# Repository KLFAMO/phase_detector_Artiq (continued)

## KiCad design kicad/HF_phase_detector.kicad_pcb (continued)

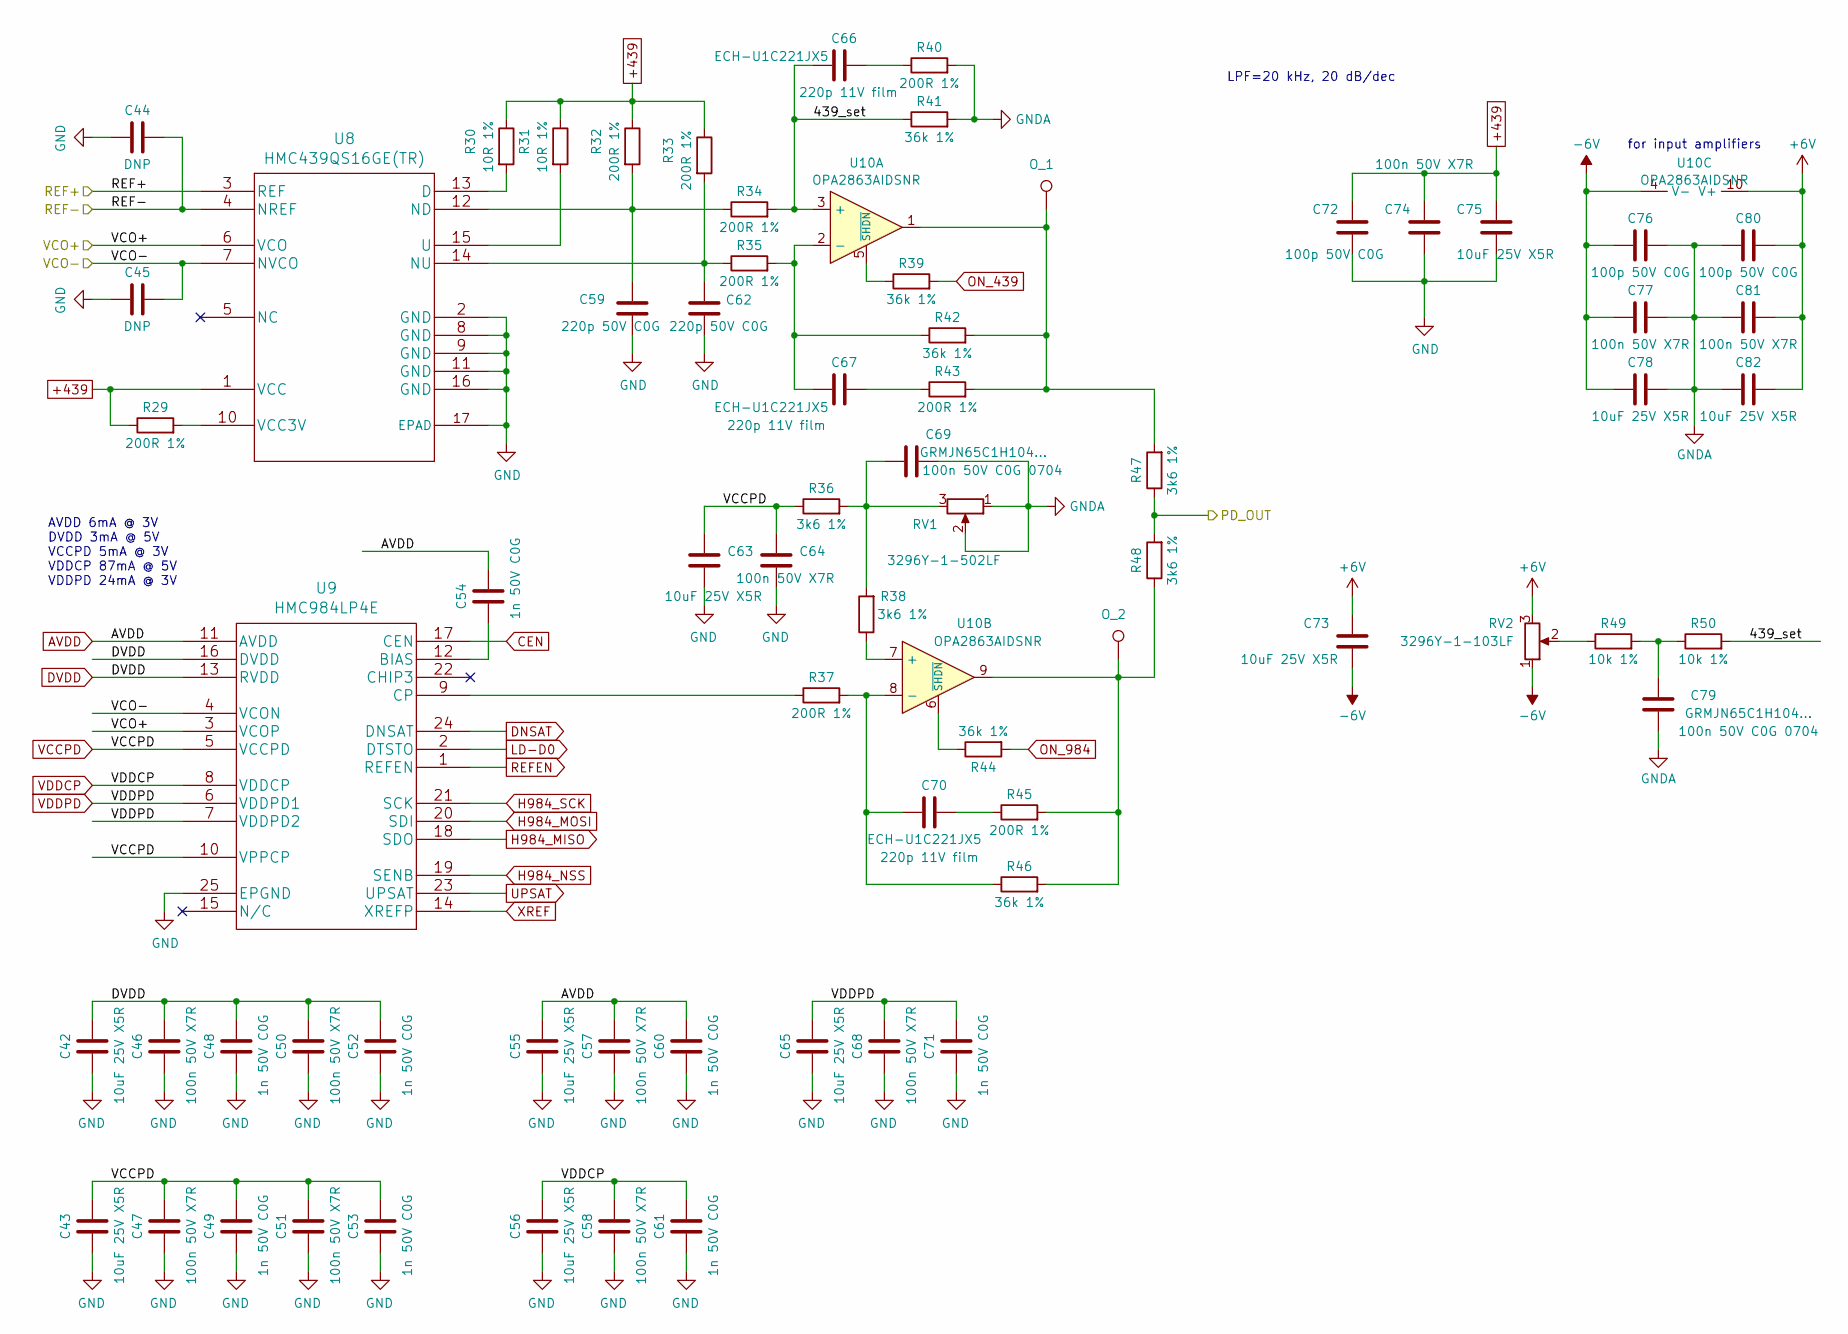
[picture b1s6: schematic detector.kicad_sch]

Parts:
C42, C43, C55, C56, C63, C65, C73, C75, C78, C82: GRM188R61E106KA73; C_0603_1608Metric
C44, C45: DNP; C_0603_1608Metric
C46, C47, C50, C51, C57, C58, C64, C68, C74, C77, C81: 100n 50V X7R; C_0603_1608Metric
C48, C49, C52, C53, C54, C60, C61, C71: 1n 50V C0G; C_0603_1608Metric
C59, C62: 220p 50V C0G; C_0603_1608Metric
C66, C67, C70: ECH-U1C221JX5; C_0603_1608Metric
C69, C79: GRMJN65C1H104...; C_0805_2012Metric
C72, C76, C80: 100p 50V C0G; C_0603_1608Metric
O_1, O_2: TestPoint; TestPoint_THTPad_1.5x1.5mm_Drill0.7mm
R29: 200R 1%; R_0805_2012Metric
R30, R31: 10R 1%; R_0603_1608Metric
R32, R33, R34, R35, R37, R40, R43, R45: 200R 1%; R_0603_1608Metric
R36, R38, R47, R48: 3k6 1%; R_0603_1608Metric
R39, R41, R42, R44, R46: 36k 1%; R_0603_1608Metric
R49, R50: 10k 1%; R_0603_1608Metric
RV1: 3296Y-1-502LF; Potentiometer_Bourns_3296Y_Vertical
RV2: 3296Y-1-103LF; Potentiometer_Bourns_3296Y_Vertical
U8: HMC439QS16GE(TR); QS16GE_ADI
U9: HMC984LP4E; QFN-24-1EP_4x4mm_P0.5mm_EP2.15x2.15mm_ThermalVias
U10: OPA2863AIDSNR; DFN-10-1EP_3x3mm_P0.5mm_EP1.65x2.38mm_ThermalVias

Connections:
/DIV14-: C44.1, U8.4 (NREF); also elsewhere on the board
/DIV24+: U8.6 (VCO), U9.3 (VCOP); also elsewhere on the board
/DIV24-: C45.1, U8.7 (NVCO), U9.4 (VCON); also elsewhere on the board
/PI and outputs/PD_OUT_set: R47.1, R48.2; also elsewhere on the board
/Phase detector/439_set: C66.1, R34.2, R41.1, R50.2, U10.3 (+)
AVDD: C54.2, C55.2, C57.1, C60.1, U9.11 (AVDD); also elsewhere on the board
CEN: U9.17 (CEN); also elsewhere on the board
DNSAT: U9.24 (DNSAT); also elsewhere on the board
DVDD: C42.2, C46.1, C48.1, C50.1, C52.1, U9.13 (RVDD), U9.16 (DVDD); also elsewhere on the board
H984_MISO: U9.18 (SDO); also elsewhere on the board
H984_MOSI: U9.20 (SDI); also elsewhere on the board
H984_NSS: U9.19 (SENB); also elsewhere on the board
H984_SCK: U9.21 (SCK); also elsewhere on the board
LD-D0: U9.2 (DTSTO); also elsewhere on the board
unnamed: C66.2, R40.1
unnamed: C67.2, R43.1
unnamed: C69.1, R36.2, R38.2, RV1.3
unnamed: C70.2, R45.1
unnamed: C79.1, R49.2, R50.1
unnamed: O_1.1, R42.2, R43.2, R47.2, U10.1
unnamed: O_2.1, R45.2, R46.2, R48.1, U10.9
unnamed: R49.1, RV2.2
unnamed: R30.2, U8.13 (D)
unnamed: C59.2, R32.2, R34.1, U8.12 (ND)
unnamed: C62.2, R33.2, R35.1, U8.14 (NU)
unnamed: R31.2, U8.15 (U)
unnamed: R29.2, U8.10 (VCC3V)
unnamed: C54.1, U9.12 (BIAS)
unnamed: R37.1, U9.9 (CP)
unnamed: C67.1, R35.2, R42.1, U10.2 (-)
unnamed: R39.1, U10.5 (~SHDN)
unnamed: R38.1, U10.7 (+)
unnamed: C70.1, R37.2, R46.1, U10.8 (-)
unnamed: R44.1, U10.6 (~SHDN)
ON_439: R39.2; also elsewhere on the board
ON_984: R44.2; also elsewhere on the board
REFEN: U9.1 (REFEN); also elsewhere on the board
UPSAT: U9.23 (UPSAT); also elsewhere on the board
VCCPD: C43.2, C47.1, C49.1, C51.1, C53.1, C63.2, C64.1, R36.1, U9.5 (VCCPD), U9.10 (VPPCP); also elsewhere on the board
VDDCP: C56.2, C58.1, C61.1, U9.8 (VDDCP); also elsewhere on the board
VDDPD: C65.2, C68.1, C71.1, U9.6 (VDDPD1), U9.7 (VDDPD2); also elsewhere on the board
XREF: U9.14 (XREFP); also elsewhere on the board

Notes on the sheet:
AVDD 6mA @ 3V DVDD 3mA @ 5V VCCPD 5mA @ 3V VDDCP 87mA @ 5V VDDPD 24mA @ 3V
for input amplifiers
LPF=20 kHz, 20 dB/dec

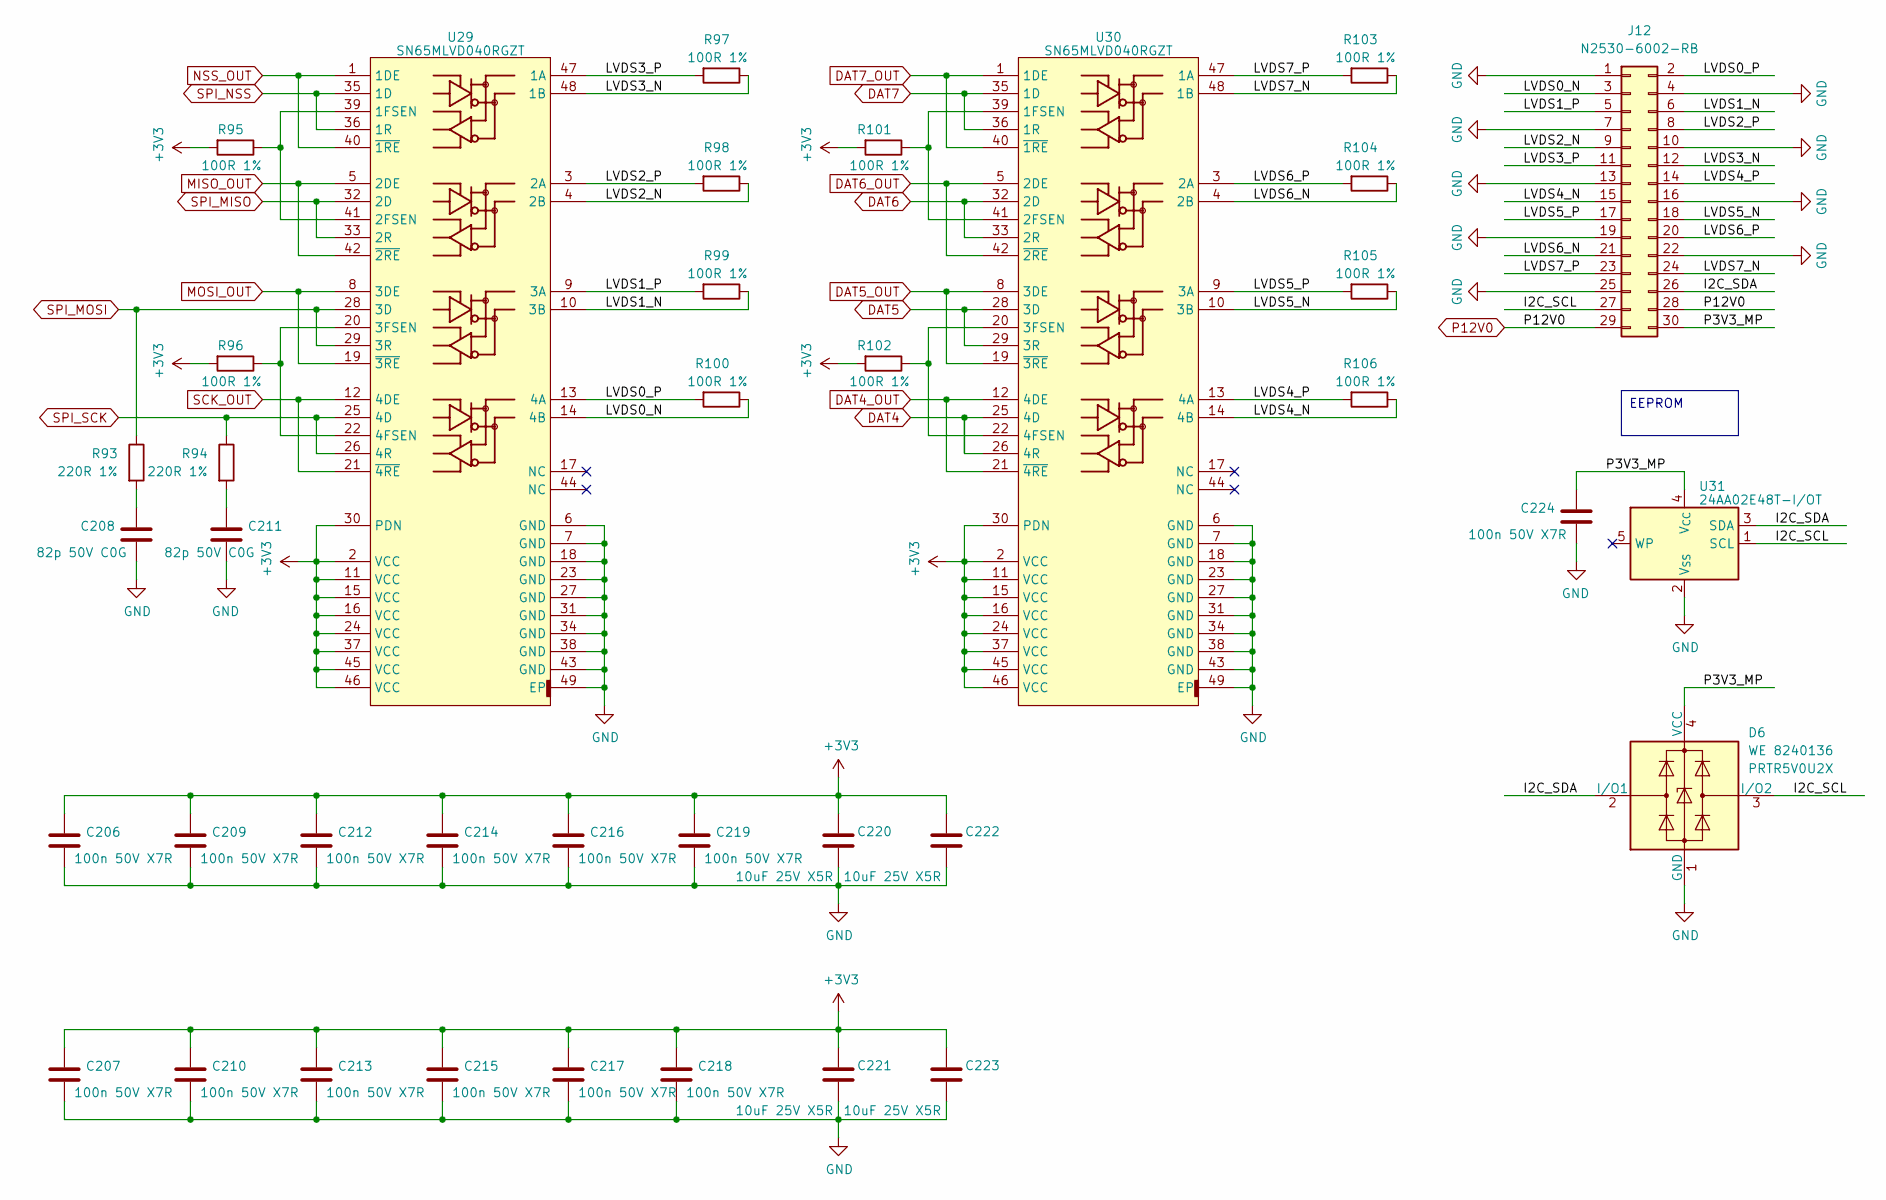
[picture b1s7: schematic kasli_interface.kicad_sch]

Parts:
C206, C207, C209, C210, C212, C213, C214, C215, C216, C217, C218, C219, C224: 100n 50V X7R; C_0603_1608Metric
C208, C211: 82p 50V C0G; C_0603_1608Metric
C220, C221, C222, C223: GRM188R61E106KA73; C_0603_1608Metric
D6: WE 8240136; SOT-143
J12: N2530-6002-RB; IDC-Header_2x15_P2.54mm_Vertical
R93, R94: 220R 1%; R_0603_1608Metric
R95, R96, R97, R98, R99, R100, R101, R102, R103, R104, R105, R106: 100R 1%; R_0603_1608Metric
U29, U30: SN65MLVD040RGZT; VQFN-48-1EP_7x7mm_P0.5mm_EP4.1x4.1mm_ThermalVias
U31: 24AA02E48T-I/OT; SOT-23-5

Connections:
/Kasli interface1/I2C_SCL: D6.3 (I/O2), J12.27, U31.1 (SCL)
/Kasli interface1/I2C_SDA: D6.2 (I/O1), J12.26, U31.3 (SDA)
/Kasli interface1/LVDS0_N: J12.3, R100.1, U29.14 (4B)
/Kasli interface1/LVDS0_P: J12.2, R100.2, U29.13 (4A)
/Kasli interface1/LVDS1_N: J12.6, R99.1, U29.10 (3B)
/Kasli interface1/LVDS1_P: J12.5, R99.2, U29.9 (3A)
/Kasli interface1/LVDS2_N: J12.9, R98.1, U29.4 (2B)
/Kasli interface1/LVDS2_P: J12.8, R98.2, U29.3 (2A)
/Kasli interface1/LVDS3_N: J12.12, R97.1, U29.48 (1B)
/Kasli interface1/LVDS3_P: J12.11, R97.2, U29.47 (1A)
/Kasli interface1/LVDS4_N: J12.15, R106.1, U30.14 (4B)
/Kasli interface1/LVDS4_P: J12.14, R106.2, U30.13 (4A)
/Kasli interface1/LVDS5_N: J12.18, R105.1, U30.10 (3B)
/Kasli interface1/LVDS5_P: J12.17, R105.2, U30.9 (3A)
/Kasli interface1/LVDS6_N: J12.21, R104.1, U30.4 (2B)
/Kasli interface1/LVDS6_P: J12.20, R104.2, U30.3 (2A)
/Kasli interface1/LVDS7_N: J12.24, R103.1, U30.48 (1B)
/Kasli interface1/LVDS7_P: J12.23, R103.2, U30.47 (1A)
/Kasli interface1/P3V3_MP: C224.1, D6.4 (VCC), J12.30, U31.4 (V_{CC})
DAT4: U30.25 (4D), U30.26 (4R); also elsewhere on the board
DAT4_OUT: U30.12 (4DE), U30.21 (~4RE); also elsewhere on the board
DAT5: U30.28 (3D), U30.29 (3R); also elsewhere on the board
DAT5_OUT: U30.8 (3DE), U30.19 (~3RE); also elsewhere on the board
DAT6: U30.32 (2D), U30.33 (2R); also elsewhere on the board
DAT6_OUT: U30.5 (2DE), U30.42 (~2RE); also elsewhere on the board
DAT7: U30.35 (1D), U30.36 (1R); also elsewhere on the board
DAT7_OUT: U30.1 (1DE), U30.40 (~1RE); also elsewhere on the board
MISO_OUT: U29.5 (2DE), U29.42 (~2RE); also elsewhere on the board
MOSI_OUT: U29.8 (3DE), U29.19 (~3RE); also elsewhere on the board
NSS_OUT: U29.1 (1DE), U29.40 (~1RE); also elsewhere on the board
unnamed: C208.1, R93.2
unnamed: C211.1, R94.2
unnamed: R95.1, U29.39 (1FSEN), U29.41 (2FSEN)
unnamed: R96.1, U29.20 (3FSEN), U29.22 (4FSEN)
unnamed: R101.1, U30.39 (1FSEN), U30.41 (2FSEN)
unnamed: R102.1, U30.20 (3FSEN), U30.22 (4FSEN)
SCK_OUT: U29.12 (4DE), U29.21 (~4RE); also elsewhere on the board
SPI_MISO: U29.32 (2D), U29.33 (2R); also elsewhere on the board
SPI_MOSI: R93.1, U29.28 (3D), U29.29 (3R); also elsewhere on the board
SPI_NSS: U29.35 (1D), U29.36 (1R); also elsewhere on the board
SPI_SCK: R94.1, U29.25 (4D), U29.26 (4R); also elsewhere on the board

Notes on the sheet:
EEPROM

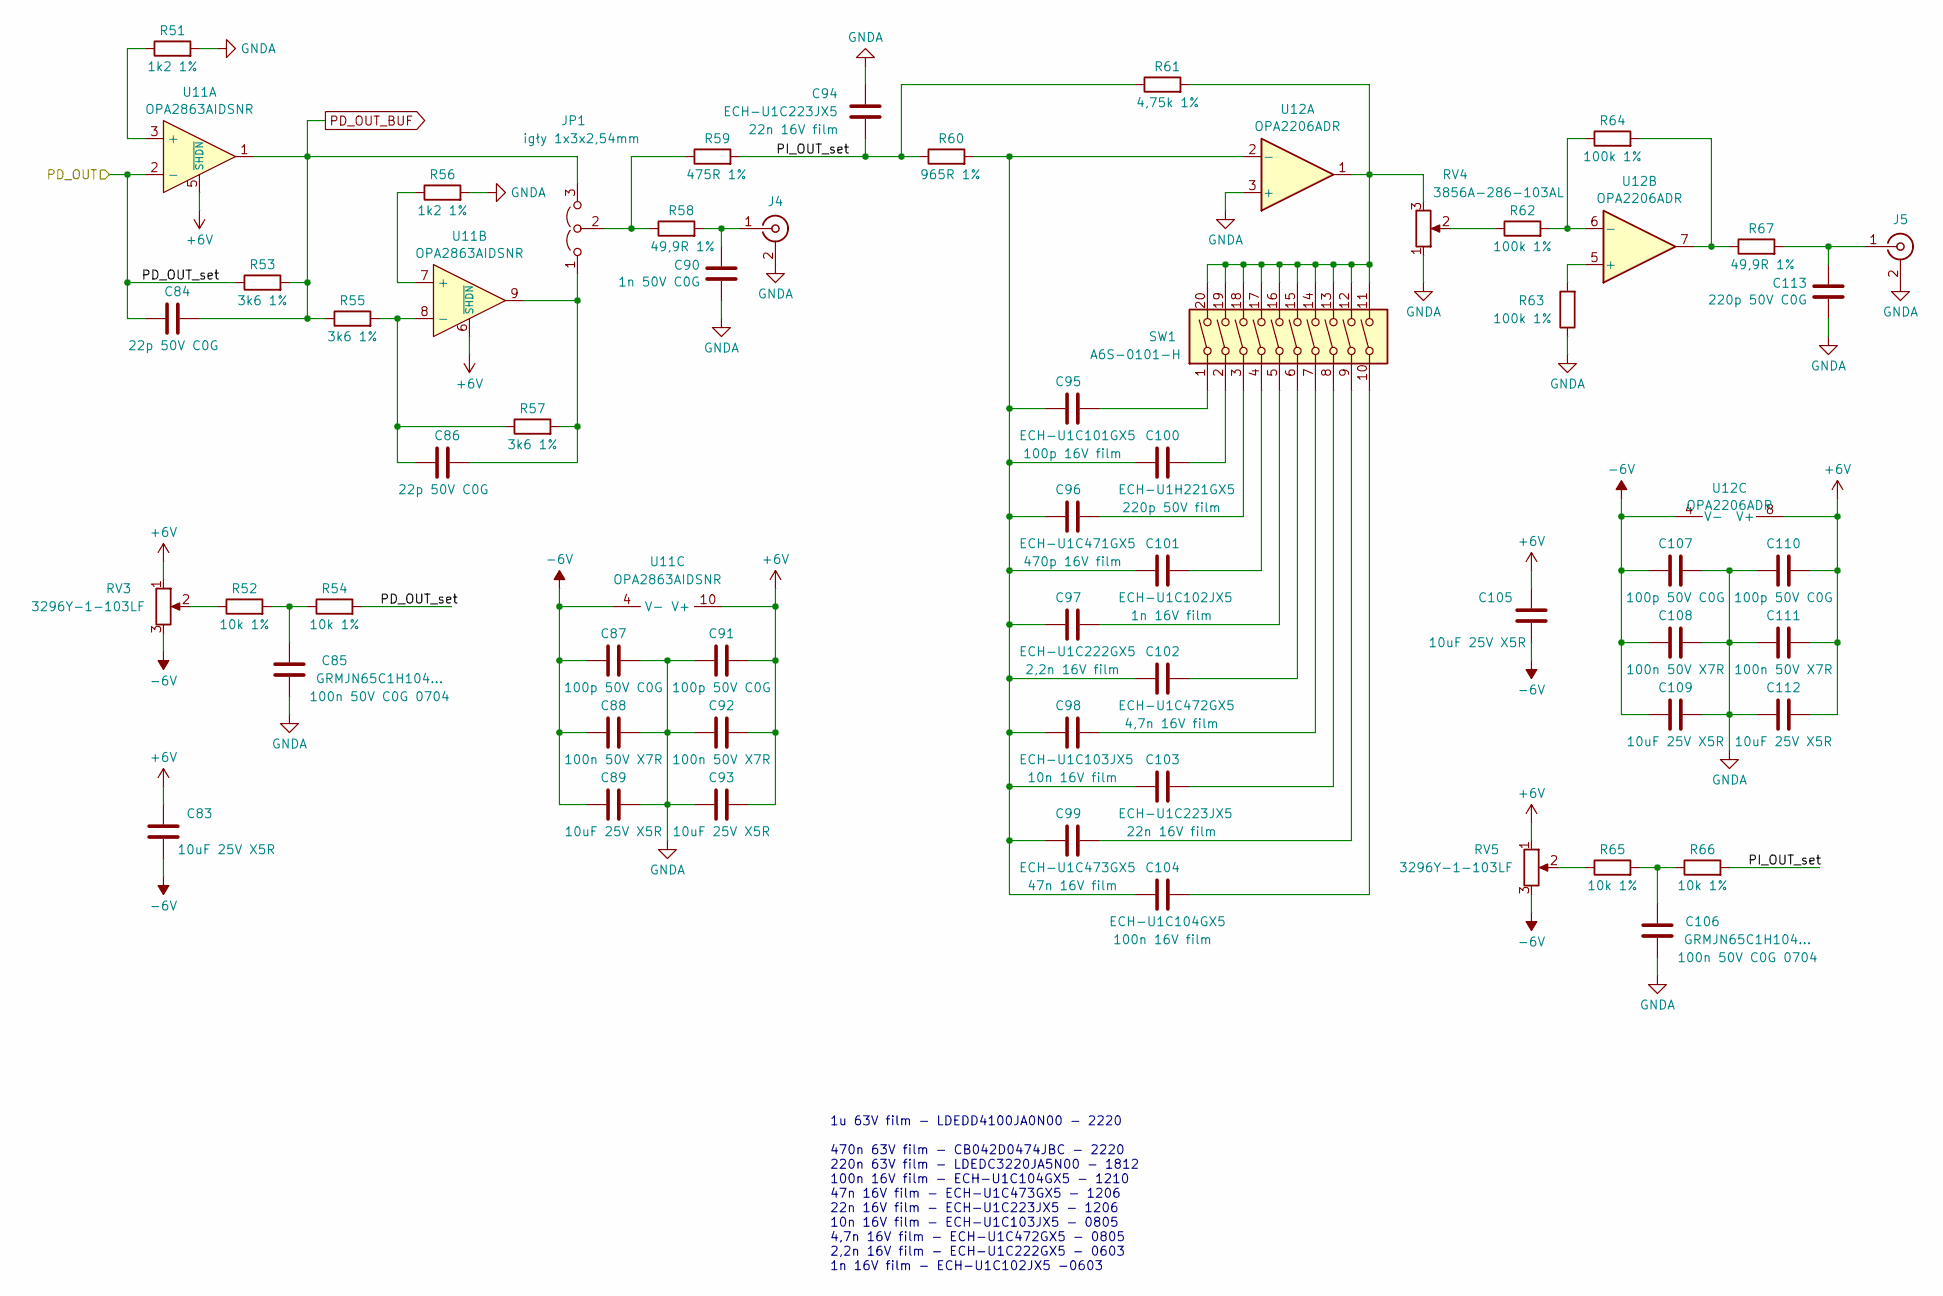
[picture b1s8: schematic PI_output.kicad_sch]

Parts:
C83, C89, C93, C105, C109, C112: GRM188R61E106KA73; C_0603_1608Metric
C84, C86: 22p 50V C0G; C_0603_1608Metric
C85, C106: GRMJN65C1H104...; C_0805_2012Metric
C87, C91, C107, C110: 100p 50V C0G; C_0603_1608Metric
C88, C92, C108, C111: 100n 50V X7R; C_0603_1608Metric
C90: 1n 50V C0G; C_0603_1608Metric
C94, C103: ECH-U1C223JX5; C_1206_3216Metric
C95: ECH-U1C101GX5; C_0603_1608Metric
C96: ECH-U1C471GX5; C_0603_1608Metric
C97: ECH-U1C222GX5; C_0603_1608Metric
C98: ECH-U1C103JX5; C_0805_2012Metric
C99: ECH-U1C473GX5; C_1206_3216Metric
C100: ECH-U1H221GX5; C_0805_2012Metric
C101: ECH-U1C102JX5; C_0603_1608Metric
C102: ECH-U1C472GX5; C_0805_2012Metric
C104: ECH-U1C104GX5; C_1210_3225Metric
C113: 220p 50V C0G; C_0603_1608Metric
J4, J5: RF2-49B-T-00-50-G-HDW; SMA_Amphenol_132203-12_Horizontal
JP1: igły 1x3x2,54mm; PinHeader_1x03_P2.54mm_Vertical
R51, R56: 1k2 1%; R_0603_1608Metric
R52, R54, R65, R66: 10k 1%; R_0603_1608Metric
R53, R55, R57: 3k6 1%; R_0603_1608Metric
R58, R67: 49,9R 1%; R_0603_1608Metric
R59: 475R 1%; R_0603_1608Metric
R60: 965R 1%; R_0603_1608Metric
R61: 4,75k 1%; R_0603_1608Metric
R62, R63, R64: 100k 1%; R_0603_1608Metric
RV3, RV5: 3296Y-1-103LF; Potentiometer_Bourns_3296Y_Vertical
RV4: 3856A-286-103AL; Potentiometer_Bourns_3856A-286_horizontal
SW1: A6S-0101-H; SW_DIP_SPSTx10_Slide_9.78x27.58mm_W8.61mm_P2.54mm
U11: OPA2863AIDSNR; DFN-10-1EP_3x3mm_P0.5mm_EP1.65x2.38mm_ThermalVias
U12: OPA2206ADR; SOIC-8_3.9x4.9mm_P1.27mm

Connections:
/PI and outputs/PD_OUT_set: C84.1, R53.1, R54.2, U11.2 (-); also elsewhere on the board
/PI and outputs/PI_OUT_set: C94.1, R59.2, R60.1, R61.1, R66.2
unnamed: C85.1, R52.2, R54.1
unnamed: C95.2, SW1.1
unnamed: C96.2, SW1.3
unnamed: C97.2, SW1.5
unnamed: C98.2, SW1.7
unnamed: C99.2, SW1.9
unnamed: C100.2, SW1.2
unnamed: C101.2, SW1.4
unnamed: C102.2, SW1.6
unnamed: C103.2, SW1.8
unnamed: C104.2, SW1.10
unnamed: C106.1, R65.2, R66.1
unnamed: C90.2, J4.1 (In), R58.2
unnamed: C113.2, J5.1 (In), R67.2
unnamed: C86.2, JP1.1 (A), R57.2, U11.9
unnamed: JP1.2 (C), R58.1, R59.1
unnamed: R52.1, RV3.2
unnamed: R61.2, RV4.3, SW1.11, SW1.12, SW1.13, SW1.14, SW1.15, SW1.16, SW1.17, SW1.18, SW1.19, SW1.20, U12.1
unnamed: R62.1, RV4.2
unnamed: R64.2, R67.1, U12.7
unnamed: R65.1, RV5.2
unnamed: R51.1, U11.3 (+)
unnamed: R56.1, U11.7 (+)
unnamed: C86.1, R55.2, R57.1, U11.8 (-)
unnamed: C95.1, C96.1, C97.1, C98.1, C99.1, C100.1, C101.1, C102.1, C103.1, C104.1, R60.2, U12.2 (-)
unnamed: R63.2, U12.5 (+)
unnamed: R62.2, R64.1, U12.6 (-)
PD_OUT_BUF: C84.2, JP1.3 (B), R53.2, R55.1, U11.1; also elsewhere on the board

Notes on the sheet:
1u 63V film - LDEDD4100JA0N00 - 2220 470n 63V film - CB042D0474JBC - 2220 220n 63V film - LDEDC3220JA5N00 - 1812 100n 16V film - ECH-U1C104GX5 - 1210 47n 16V film - ECH-U1C473GX5 - 1206 22n 16V film - ECH-U1C223JX5 - 1206 10n 16V film - ECH-U1C103JX5 - 0805 4,7n 16V film - ECH-U1C472GX5 - 0805 2,2n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

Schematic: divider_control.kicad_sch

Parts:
C38: 1n 50V C0G; C_0603_1608Metric
C39: 100p 50V C0G; C_0603_1608Metric
C40: 100n 50V X7R; C_0603_1608Metric
C41: GRM188R61E106KA73; C_0603_1608Metric
D3: BAT54SW...; SOT-323_SC-70
J3: RF2-49B-T-00-50-G-HDW; SMA_Amphenol_132203-12_Horizontal
R23: 49,9R 1%; R_0603_1608Metric
R24, R25: 680R 1%; R_0603_1608Metric
R26, R27: 60,4k 1%; R_0603_1608Metric
R28: 150k 1%; R_0603_1608Metric
U6: TBD62003AFNG,EL; SSOP-16_4.4x5.2mm_P0.65mm
U7: TLV3603DCKx; SOT-363_SC-70-6

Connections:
10MHz_in: U7.1; also elsewhere on the board
/Inputs and prescalers/DIV1_S0: U6.12 (O5); also elsewhere on the board
/Inputs and prescalers/DIV1_S1: U6.11 (O6); also elsewhere on the board
/Inputs and prescalers/DIV1_S2: R27.1; also elsewhere on the board
/Inputs and prescalers/DIV2_S0: U6.16 (O1); also elsewhere on the board
/Inputs and prescalers/DIV2_S1: U6.15 (O2); also elsewhere on the board
/Inputs and prescalers/DIV2_S2: R26.1; also elsewhere on the board
unnamed: C38.1, R23.1, R24.2
unnamed: D3.3 (COM), R24.1, U7.3 (+)
unnamed: C38.2, J3.1 (In)
unnamed: R26.2, U6.14 (O3)
unnamed: R27.2, U6.10 (O7)
unnamed: R25.1, U7.4 (-)
unnamed: R28.1, U7.5 (~LE)
iDIV1_S0: U6.5 (I5); also elsewhere on the board
iDIV1_S1: U6.6 (I6); also elsewhere on the board
iDIV1_S2: U6.7 (I7); also elsewhere on the board
iDIV2_S0: U6.1 (I1); also elsewhere on the board
iDIV2_S1: U6.2 (I2); also elsewhere on the board
iDIV2_S2: U6.3 (I3); also elsewhere on the board

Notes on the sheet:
degree of division iDIVx_S0 iDIVx_S1 iDIVx_S2 1 H H H 2 L H H 4 H H L 8 H L L 16 L L L see page 4-5 of https://www.ti.com/lit/ds/symlink/cdcm1804.pdf
10 MHz input

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
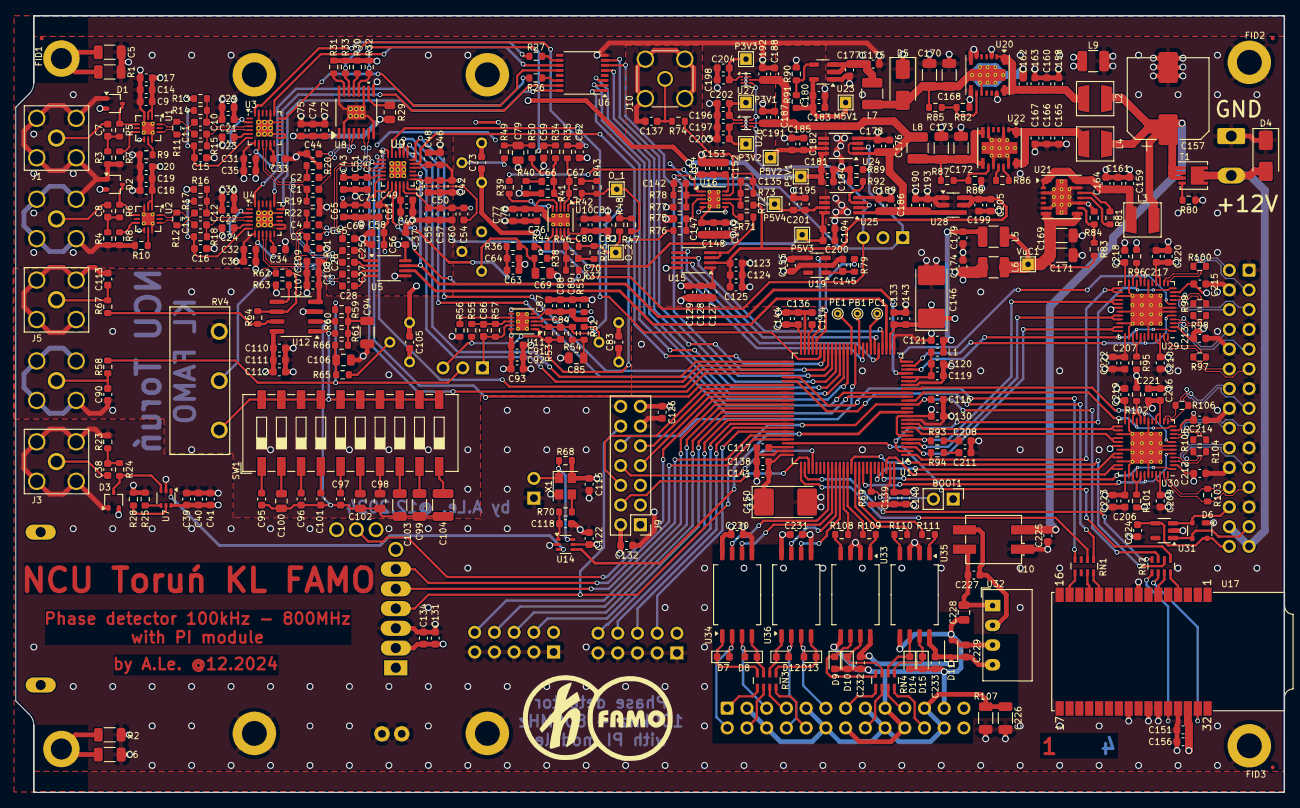
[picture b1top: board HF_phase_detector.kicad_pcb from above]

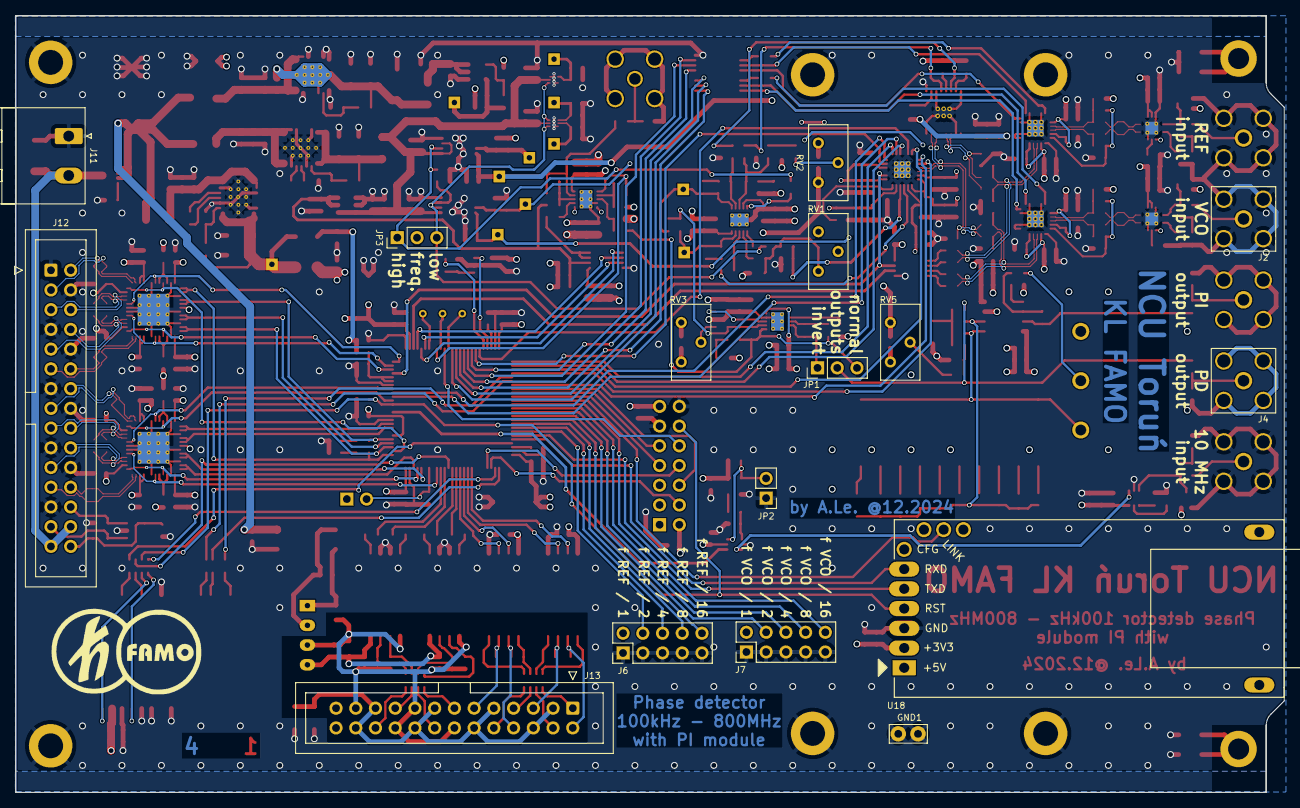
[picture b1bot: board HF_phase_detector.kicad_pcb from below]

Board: 4 copper layers, 163.3 x 100.0 mm, 461 parts (17 on the bottom side), 284 nets.

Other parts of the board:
C157: AEA1010471M025R; CP_Elec_10x10
C167, C178, C182: 100n 50V X7R; C_0603_1608Metric
C173: GRM31CR61A476KE15L; C_1206_3216Metric
J11: MSTBA 2,5/ 2-G-5,08 1757242; PhoenixContact_MSTBA_2,5_2-G-5,08_1x02_P5.08mm_Horizontal
L4: LQH44NN101K03L; L_MURATA_LQH44
L8: LQH32PN100MNCL; L_1210_3225Metric
P5V2: TestPoint; TestPoint_THTPad_1.5x1.5mm_Drill0.7mm

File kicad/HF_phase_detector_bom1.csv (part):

"Source:","D:\Projekty\FAMO\HF_phase_detector\HF_phase_detector.kicad_sch"
"Date:","07.01.2025 11:11:47"
"Tool:","Eeschema 7.0.11"
"Generator:","C:\Program Files\KiCad\bin\scripting\plugins/bom_csv_grouped_by_value.py"
"Component Count:","459"

"Individual Components:"

"Item","Qty","Reference(s)","Value","LibPart","Footprint","Datasheet","Comm","Sim.Device","Sim.Enable","Sim.Pins"
"","","BOOT1","DNP","Connector_Generic:Conn_01x02","Connector_PinHeader_2.54mm:PinHeader_1x02_P2.54mm_Vertical","~","igły 2x1x2,54","","",""
"","","C1","15n 25V C0G","Device:C","Capacitor_SMD:C_0603_1608Metric","~","","","",""
"","","C2","15n 25V C0G","Device:C","Capacitor_SMD:C_0603_1608Metric","~","","","",""
"","","C3","15n 25V C0G","Device:C","Capacitor_SMD:C_0603_1608Metric","~","","","",""
"","","C4","15n 25V C0G","Device:C","Capacitor_SMD:C_0603_1608Metric","~","","","",""
"","","C5","GCJ31BR73A102KXJ1L","Device:C","Capacitor_SMD:C_1206_3216Metric","~","1n 1kV X7R","","",""
"","","C6","GCJ31BR73A102KXJ1L","Device:C","Capacitor_SMD:C_1206_3216Metric","~","1n 1kV X7R","","",""
"","","C7","15n 25V C0G","Device:C","Capacitor_SMD:C_0603_1608Metric","~","","","",""
"","","C8","15n 25V C0G","Device:C","Capacitor_SMD:C_0603_1608Metric","~","","","",""
"","","C9","100p 50V C0G","Device:C","Capacitor_SMD:C_0603_1608Metric","~","","","",""
"","","C10","15n 25V C0G","Device:C","Capacitor_SMD:C_0603_1608Metric","~","","","",""
"","","C11","15n 25V C0G","Device:C","Capacitor_SMD:C_0603_1608Metric","~","","","",""
"","","C12","15n 25V C0G","Device:C","Capacitor_SMD:C_0603_1608Metric","~","","","",""
"","","C13","15n 25V C0G","Device:C","Capacitor_SMD:C_0603_1608Metric","~","","","",""
"","","C14","100n 50V X7R","Device:C","Capacitor_SMD:C_0603_1608Metric","~","","","",""
"","","C15","15n 25V C0G","Device:C","Capacitor_SMD:C_0603_1608Metric","~","","","",""
"","","C16","15n 25V C0G","Device:C","Capacitor_SMD:C_0603_1608Metric","~","","","",""
"","","C17","GRM188R61E106KA73","Device:C","Capacitor_SMD:C_0603_1608Metric","~","10uF 25V X5R","","",""
"","","C18","100p 50V C0G","Device:C","Capacitor_SMD:C_0603_1608Metric","~","","","",""
"","","C19","100n 50V X7R","Device:C","Capacitor_SMD:C_0603_1608Metric","~","","","",""
"","","C20","GRM188R61E106KA73","Device:C","Capacitor_SMD:C_0603_1608Metric","~","10uF 25V X5R","","",""
"","","C21","100n 50V X7R","Device:C","Capacitor_SMD:C_0603_1608Metric","~","","","",""
"","","C22","100n 50V X7R","Device:C","Capacitor_SMD:C_0603_1608Metric","~","","","",""
"","","C23","100n 50V X7R","Device:C","Capacitor_SMD:C_0603_1608Metric","~","","","",""
"","","C24","100n 50V X7R","Device:C","Capacitor_SMD:C_0603_1608Metric","~","","","",""
"","","C25","15n 25V C0G","Device:C","Capacitor_SMD:C_0603_1608Metric","~","","","",""
"","","C26","15n 25V C0G","Device:C","Capacitor_SMD:C_0603_1608Metric","~","","","",""
"","","C27","15n 25V C0G","Device:C","Capacitor_SMD:C_0603_1608Metric","~","","","",""
"","","C28","15n 25V C0G","Device:C","Capacitor_SMD:C_0603_1608Metric","~","","","",""
"","","C29","GRM188R61E106KA73","Device:C","Capacitor_SMD:C_0603_1608Metric","~","10uF 25V X5R","","",""
"","","C30","GRM188R61E106KA73","Device:C","Capacitor_SMD:C_0603_1608Metric","~","10uF 25V X5R","","",""
"","","C31","100n 50V X7R","Device:C","Capacitor_SMD:C_0603_1608Metric","~","","","",""
"","","C32","100n 50V X7R","Device:C","Capacitor_SMD:C_0603_1608Metric","~","","","",""
"","","C33","100n 50V X7R","Device:C","Capacitor_SMD:C_0603_1608Metric","~","","","",""
"","","C34","100n 50V X7R","Device:C","Capacitor_SMD:C_0603_1608Metric","~","","","",""
"","","C35","GRM188R61E106KA73","Device:C","Capacitor_SMD:C_0603_1608Metric","~","10uF 25V X5R","","",""
"","","C36","GRM188R61E106KA73","Device:C","Capacitor_SMD:C_0603_1608Metric","~","10uF 25V X5R","","",""
"","","C37","100n 50V X7R","Device:C","Capacitor_SMD:C_0603_1608Metric","~","","","",""
"","","C38","1n 50V C0G","Device:C","Capacitor_SMD:C_0603_1608Metric","~","","","",""
"","","C39","100p 50V C0G","Device:C","Capacitor_SMD:C_0603_1608Metric","~","","","",""
"","","C40","100n 50V X7R","Device:C","Capacitor_SMD:C_0603_1608Metric","~","","","",""
"","","C41","GRM188R61E106KA73","Device:C","Capacitor_SMD:C_0603_1608Metric","~","10uF 25V X5R","","",""
"","","C42","GRM188R61E106KA73","Device:C","Capacitor_SMD:C_0603_1608Metric","~","10uF 25V X5R","","",""
"","","C43","GRM188R61E106KA73","Device:C","Capacitor_SMD:C_0603_1608Metric","~","10uF 25V X5R","","",""
"","","C44","DNP","Device:C","Capacitor_SMD:C_0603_1608Metric","~","15n 25V C0G","","",""
"","","C45","DNP","Device:C","Capacitor_SMD:C_0603_1608Metric","~","15n 25V C0G","","",""
"","","C46","100n 50V X7R","Device:C","Capacitor_SMD:C_0603_1608Metric","~","","","",""
"","","C47","100n 50V X7R","Device:C","Capacitor_SMD:C_0603_1608Metric","~","","","",""
"","","C48","1n 50V C0G","Device:C","Capacitor_SMD:C_0603_1608Metric","~","","","",""
"","","C49","1n 50V C0G","Device:C","Capacitor_SMD:C_0603_1608Metric","~","","","",""
"","","C50","100n 50V X7R","Device:C","Capacitor_SMD:C_0603_1608Metric","~","","","",""
"","","C51","100n 50V X7R","Device:C","Capacitor_SMD:C_0603_1608Metric","~","","","",""
"","","C52","1n 50V C0G","Device:C","Capacitor_SMD:C_0603_1608Metric","~","","","",""
"","","C53","1n 50V C0G","Device:C","Capacitor_SMD:C_0603_1608Metric","~","","","",""
"","","C54","1n 50V C0G","Device:C","Capacitor_SMD:C_0603_1608Metric","~","","","",""
"","","C55","GRM188R61E106KA73","Device:C","Capacitor_SMD:C_0603_1608Metric","~","10uF 25V X5R","","",""
"","","C56","GRM188R61E106KA73","Device:C","Capacitor_SMD:C_0603_1608Metric","~","10uF 25V X5R","","",""
"","","C57","100n 50V X7R","Device:C","Capacitor_SMD:C_0603_1608Metric","~","","","",""
"","","C58","100n 50V X7R","Device:C","Capacitor_SMD:C_0603_1608Metric","~","","","",""
"","","C59","220p 50V C0G","Device:C","Capacitor_SMD:C_0603_1608Metric","~","","","",""
"","","C60","1n 50V C0G","Device:C","Capacitor_SMD:C_0603_1608Metric","~","","","",""
"","","C61","1n 50V C0G","Device:C","Capacitor_SMD:C_0603_1608Metric","~","","","",""
"","","C62","220p 50V C0G","Device:C","Capacitor_SMD:C_0603_1608Metric","~","","","",""
"","","C63","GRM188R61E106KA73","Device:C","Capacitor_SMD:C_0603_1608Metric","~","10uF 25V X5R","","",""
"","","C64","100n 50V X7R","Device:C","Capacitor_SMD:C_0603_1608Metric","~","","","",""
"","","C65","GRM188R61E106KA73","Device:C","Capacitor_SMD:C_0603_1608Metric","~","10uF 25V X5R","","",""
"","","C66","ECH-U1C221JX5","Device:C","Capacitor_SMD:C_0603_1608Metric","~","220p 11V film","","",""
"","","C67","ECH-U1C221JX5","Device:C","Capacitor_SMD:C_0603_1608Metric","~","220p 11V film","","",""
"","","C68","100n 50V X7R","Device:C","Capacitor_SMD:C_0603_1608Metric","~","","","",""
"","","C69","GRMJN65C1H104...","Device:C","Capacitor_SMD:C_0805_2012Metric","~","100n 50V C0G 0704","","",""
"","","C70","ECH-U1C221JX5","Device:C","Capacitor_SMD:C_0603_1608Metric","~","220p 11V film","","",""
"","","C71","1n 50V C0G","Device:C","Capacitor_SMD:C_0603_1608Metric","~","","","",""
"","","C72","100p 50V C0G","Device:C","Capacitor_SMD:C_0603_1608Metric","~","","","",""
"","","C73","GRM188R61E106KA73","Device:C","Capacitor_SMD:C_0603_1608Metric","~","10uF 25V X5R","","",""
"","","C74","100n 50V X7R","Device:C","Capacitor_SMD:C_0603_1608Metric","~","","","",""
"","","C75","GRM188R61E106KA73","Device:C","Capacitor_SMD:C_0603_1608Metric","~","10uF 25V X5R","","",""
"","","C76","100p 50V C0G","Device:C","Capacitor_SMD:C_0603_1608Metric","~","","","",""
"","","C77","100n 50V X7R","Device:C","Capacitor_SMD:C_0603_1608Metric","~","","","",""
"","","C78","GRM188R61E106KA73","Device:C","Capacitor_SMD:C_0603_1608Metric","~","10uF 25V X5R","","",""
"","","C79","GRMJN65C1H104...","Device:C","Capacitor_SMD:C_0805_2012Metric","~","100n 50V C0G 0704","","",""
"","","C80","100p 50V C0G","Device:C","Capacitor_SMD:C_0603_1608Metric","~","","","",""
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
